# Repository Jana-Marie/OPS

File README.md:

# OPS

OPS is a matchbox sized 65W CC/CV lab power supply. It is controlled by SCPI and powered by USB-PD.

**Please Note that this project is not yet fully tested.**

<table>
  <tbody>
    <tr>
      <td colspan="2">
        
      </td>
    </tr>
    <tr>
      <td>
        
      </td>
      <td>
        
      </td>
    </tr>
    <tr>
      <td colspan="2">
        
      </td>
    </tr>
    <tr>
      <td>
        
      </td>
      <td>
        
      </td>
    </tr>
  </tbody>
</table>

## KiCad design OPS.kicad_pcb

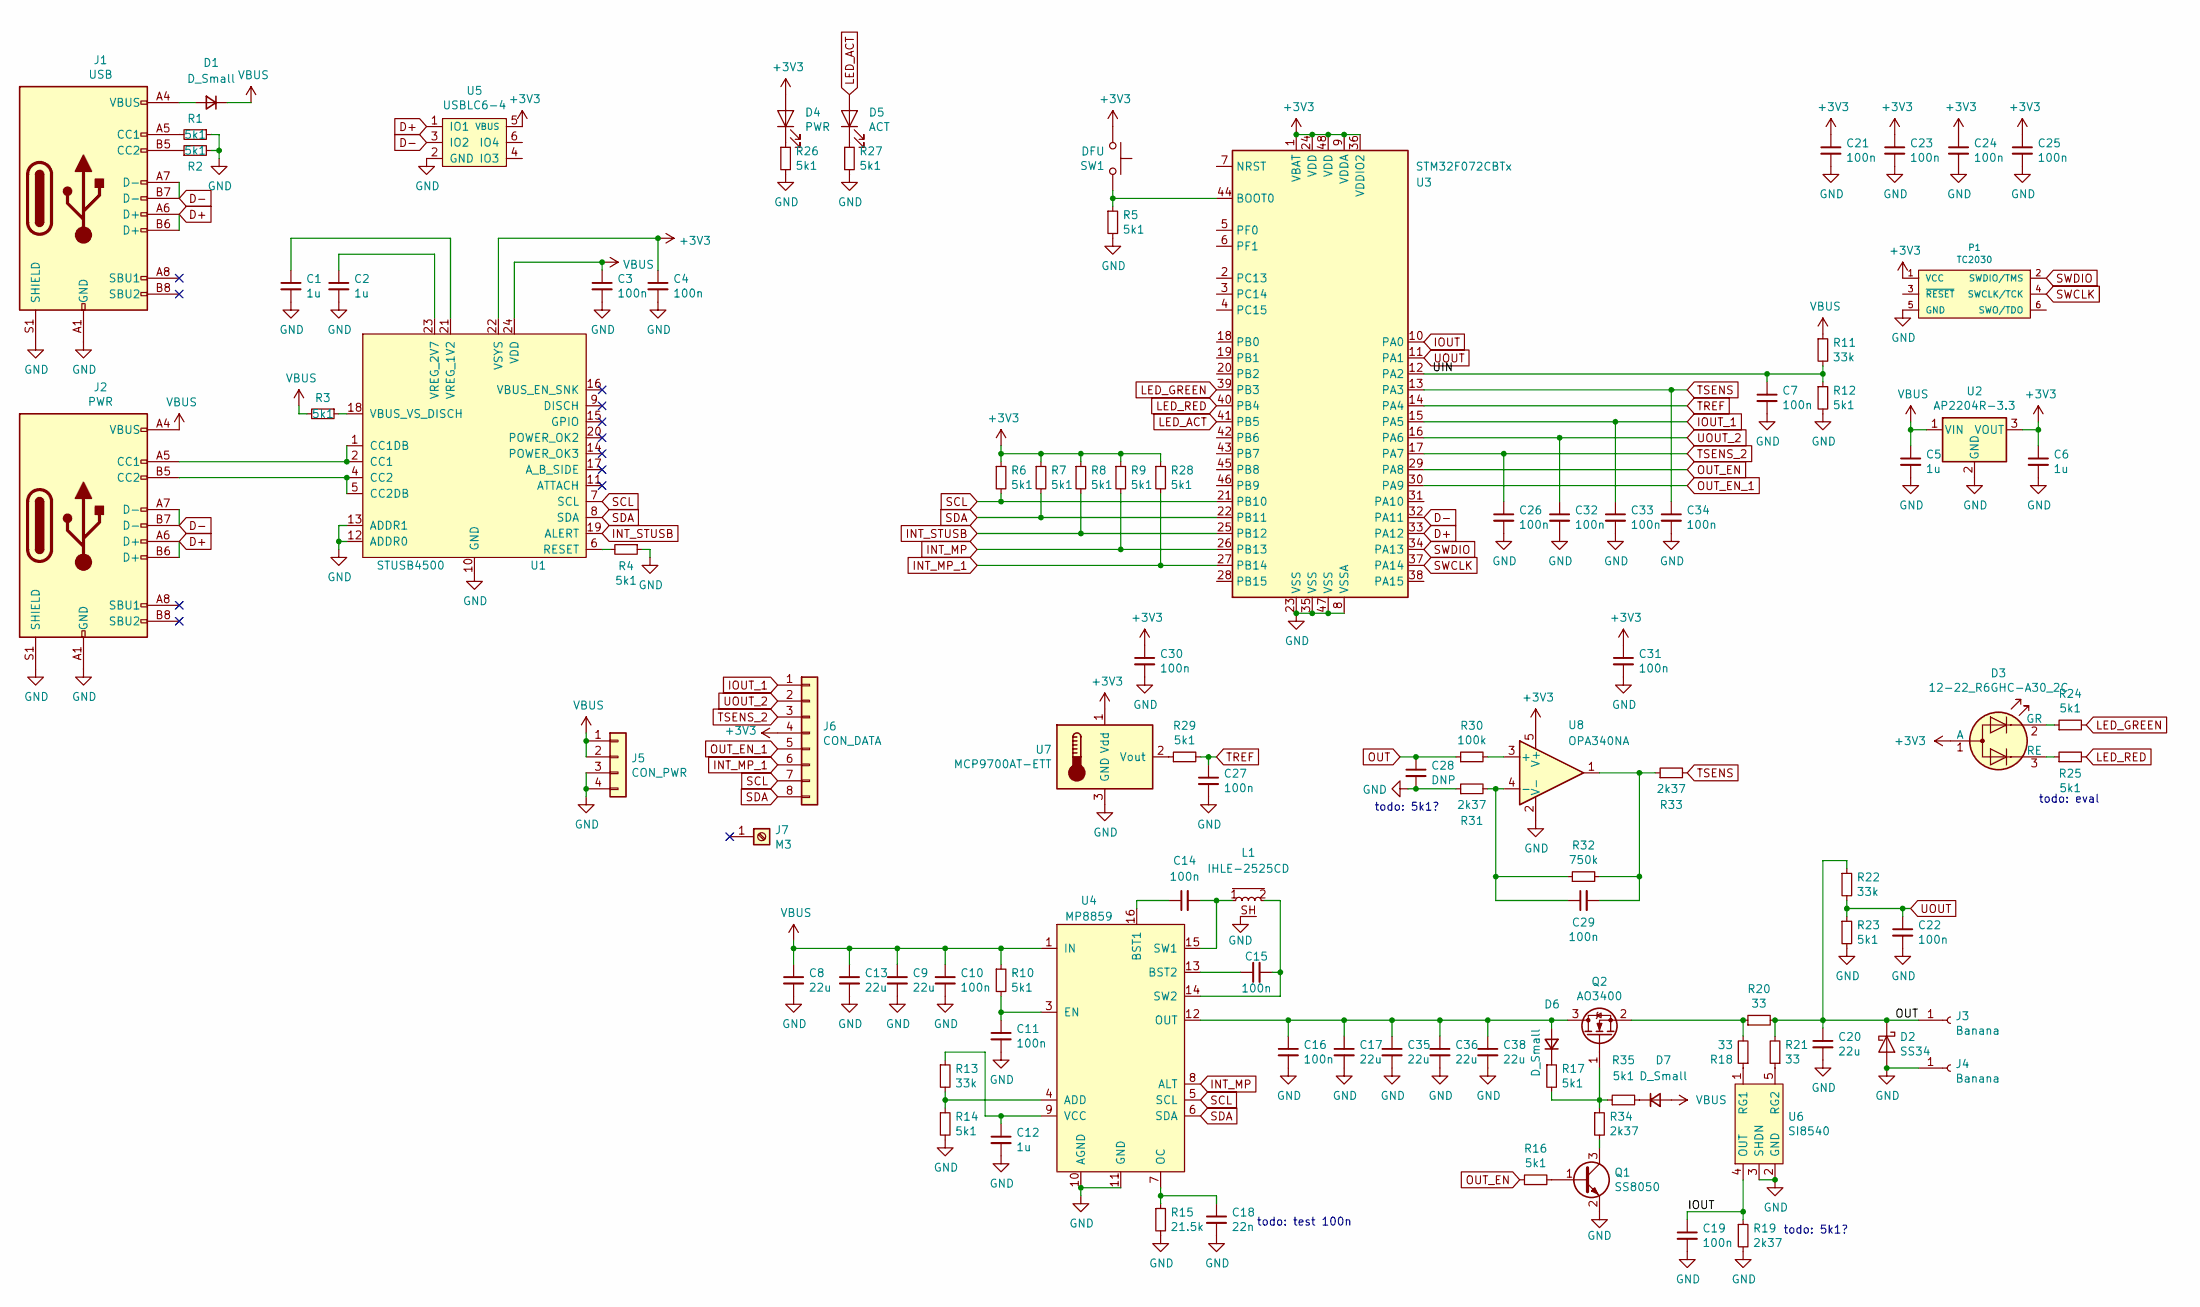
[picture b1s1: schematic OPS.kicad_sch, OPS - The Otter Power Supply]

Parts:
C1, C2, C5, C6, C12: 1u; C_0402
C3, C4, C7, C11, C19, C21, C22, C23, C24, C25, C26, C27, C29, C30, C31, C32, C33, C34: 100n; C_0402
C8, C9, C13, C17, C35, C36, C38: 22u; C_1210
C10, C14, C15, C16: 100n; C_0603
C18: 22n; C_0402
C20: 22u; C_0805
C28: DNP; C_0402
D1, D6, D7: D_Small; D_SOD-323
D2: SS34; D_SOD-123
D3: 12-22_R6GHC-A30_2C; R6GHC-A30
D4: PWR; LED_0603_1608Metric
D5: ACT; LED_0603_1608Metric
J1: USB; USB-C 16Pin
J2: PWR; USB-C 16Pin
J3, J4: Banana; banana-jack
J5: CON_PWR; PinHeader_1x04_P2.00mm_Vertical
J6: CON_DATA; PinHeader_1x08_P2.00mm_Vertical
J7: M3; MountingHole_3.2mm_M3_Pad
L1: IHLE-2525CD
P1: TC2030
Q1: SS8050; SOT-23
Q2: AO3400; SOT-23
R1, R2, R3, R4, R5, R6, R7, R8, R9, R10, R12, R14, R16, R17, R23, R24, R25, R26, R27, R28, R29, R35: 5k1; R_0402
R11, R13, R22: 33k; R_0402
R15: 21.5k; R_0402
R18, R21: 33; R_0402
R19, R31, R33, R34: 2k37; R_0402
R20: 33; R_0805
R30: 100k; R_0402
R32: 750k; R_0402
SW1: DFU; SW_SPST_EVQP7C
U1: STUSB4500; QFN-24-1EP_4x4mm_P0.5mm_EP2.7x2.7mm
U2: AP2204R-3.3; SOT-89-3
U3: STM32F072CBTx; LQFP-48_7x7mm_P0.5mm
U4: MP8859
U5: USBLC6-4; SOT-23-6
U6: SI8540; SOT-23-5
U7: MCP9700AT-ETT; SOT-23
U8: OPA340NA; SOT-23-5

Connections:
+3V3: C4.1, C6.1, C21.1, C23.1, C24.1, C25.1, C30.1, C31.1, D3.1 (A), D4.2 (A), J6.4, P1.1 (VCC), R6.1, R7.1, R8.1, R9.1, R28.1, SW1.1, U1.22 (VSYS), U2.3 (VOUT), U3.1 (VBAT), U3.9 (VDDA), U3.24 (VDD), U3.36 (VDDIO2), U3.48 (VDD), U5.5 (VBUS), U7.1 (Vdd), U8.5 (V+)
/UIN: C7.1, R11.2, R12.1, U3.12 (PA2)
D+: J1.A6 (D+), J1.B6 (D+), J2.A6 (D+), J2.B6 (D+), U3.33 (PA12), U5.1 (IO1)
D-: J1.A7 (D-), J1.B7 (D-), J2.A7 (D-), J2.B7 (D-), U3.32 (PA11), U5.3 (IO2)
GND: C1.2, C2.2, C3.2, C4.2, C5.2, C6.2, C7.2, C8.2, C9.2, C10.2, C11.2, C12.2, C13.2, C16.2, C17.2, C18.2, C19.2, C20.2, C21.2, C22.2, C23.2, C24.2, C25.2, C26.2, C27.2, C28.2, C30.2, C31.2, C32.2, C33.2, C34.2, C35.2, C36.2, C38.2, D2.2 (A), J1.A1 (GND), J1.A12 (GND), J1.B1 (GND), J1.B12 (GND), J1.S1 (SHIELD), J2.A1 (GND), J2.A12 (GND), J2.B1 (GND), J2.B12 (GND), J2.S1 (SHIELD), J4.1, J5.3, J5.4, L1.SH, P1.5 (GND), Q1.2 (E), R1.1, R2.2, R4.1, R5.2, R12.2, R14.2, R15.2, R19.2, R23.2, R26.2, R27.2, R31.1, U1.10 (GND), U1.12 (ADDR0), U1.13 (ADDR1), U1.25 (GND), U2.2 (GND), U3.8 (VSSA), U3.23 (VSS), U3.35 (VSS), U3.47 (VSS), U4.2 (GND), U4.10 (AGND), U4.11 (GND), U5.2 (GND), U6.2 (GND), U6.3 (SHDN), U7.3 (GND), U8.2 (V-)
INT_MP: R9.2, U3.26 (PB13), U4.8 (ALT)
INT_MP_1: J6.6, R28.2, U3.27 (PB14)
INT_STUSB: R8.2, U1.19 (ALERT), U3.25 (PB12)
IOUT: C19.1, R19.1, U3.10 (PA0), U6.4 (OUT)
IOUT_1: C33.1, J6.1, U3.15 (PA5)
LED_ACT: D5.2 (A), U3.41 (PB5)
LED_GREEN: R24.2, U3.39 (PB3)
LED_RED: R25.2, U3.40 (PB4)
unnamed: C1.1, U1.21 (VREG_1V2)
unnamed: C2.1, U1.23 (VREG_2V7)
unnamed: C11.1, R10.2, U4.3 (EN)
unnamed: C12.1, R13.1, U4.9 (VCC)
unnamed: C14.1, U4.16 (BST1)
unnamed: C14.2, L1.1, U4.15 (SW1)
unnamed: C15.1, U4.13 (BST2)
unnamed: C15.2, L1.2, U4.14 (SW2)
unnamed: C16.1, C17.1, C35.1, C36.1, C38.1, D6.2 (A), Q2.3 (D), U4.12 (OUT)
unnamed: C18.1, R15.1, U4.7 (OC)
unnamed: C29.1, R31.2, R32.1, U8.4 (-)
unnamed: C29.2, R32.2, R33.1, U8.1
unnamed: D1.2 (A), J1.A4 (VBUS), J1.A9 (VBUS), J1.B4 (VBUS), J1.B9 (VBUS)
unnamed: D3.2 (GR), R24.1
unnamed: D3.3 (RE), R25.1
unnamed: D4.1 (K), R26.1
unnamed: D5.1 (K), R27.1
unnamed: D6.1 (K), R17.1
unnamed: D7.1 (K), R35.2
unnamed: J1.A5 (CC1), R1.2
unnamed: J1.B5 (CC2), R2.1
unnamed: J2.A5 (CC1), U1.1 (CC1DB), U1.2 (CC1)
unnamed: J2.B5 (CC2), U1.4 (CC2), U1.5 (CC2DB)
unnamed: Q1.1 (B), R16.2
unnamed: Q1.3 (C), R34.2
unnamed: Q2.1 (G), R17.2, R34.1, R35.1
unnamed: Q2.2 (S), R18.2, R20.1
unnamed: R3.1, U1.18 (VBUS_VS_DISCH)
unnamed: R4.2, U1.6 (RESET)
unnamed: R5.1, SW1.2, U3.44 (BOOT0)
unnamed: R13.2, R14.1, U4.4 (ADD)
unnamed: R18.1, U6.1 (RG1)
unnamed: R21.1, U6.5 (RG2)
unnamed: R29.1, U7.2 (Vout)
unnamed: R30.2, U8.3 (+)
OUT: C20.1, C28.1, D2.1 (K), J3.1, R20.2, R21.2, R22.1, R30.1
OUT_EN: R16.1, U3.29 (PA8)
OUT_EN_1: J6.5, U3.30 (PA9)
SCL: J6.7, R6.2, U1.7 (SCL), U3.21 (PB10), U4.5 (SCL)
SDA: J6.8, R7.2, U1.8 (SDA), U3.22 (PB11), U4.6 (SDA)
SWCLK: P1.4 (SWCLK/TCK), U3.37 (PA14)
SWDIO: P1.2 (SWDIO/TMS), U3.34 (PA13)
TREF: C27.1, R29.2, U3.14 (PA4)
TSENS: C34.1, R33.2, U3.13 (PA3)
TSENS_2: C26.1, J6.3, U3.17 (PA7)
UOUT: C22.1, R22.2, R23.1, U3.11 (PA1)
UOUT_2: C32.1, J6.2, U3.16 (PA6)
VBUS: C3.1, C5.1, C8.1, C9.1, C10.1, C13.1, D1.1 (K), D7.2 (A), J2.A4 (VBUS), J2.A9 (VBUS), J2.B4 (VBUS), J2.B9 (VBUS), J5.1, J5.2, R3.2, R10.1, R11.1, U1.24 (VDD), U2.1 (VIN), U4.1 (IN)

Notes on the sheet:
todo: 5k1?
todo: eval
todo: test 100n

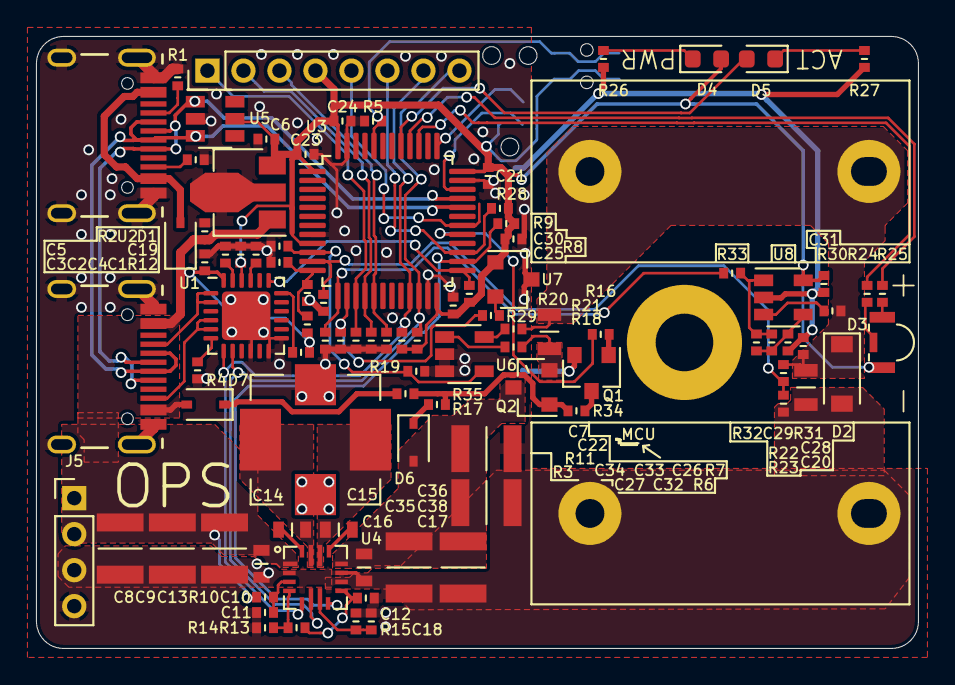
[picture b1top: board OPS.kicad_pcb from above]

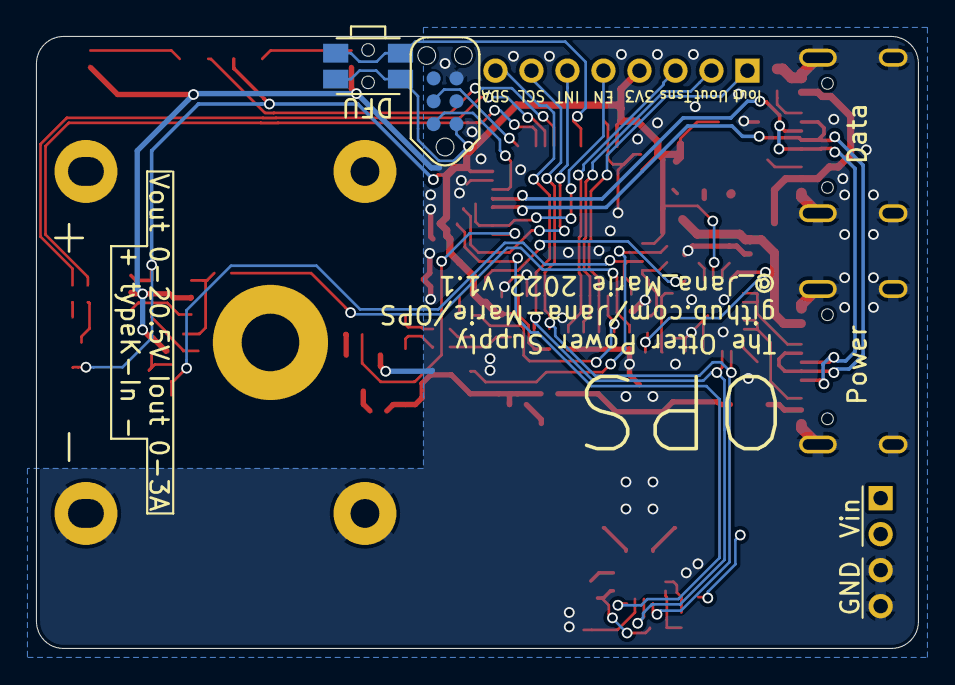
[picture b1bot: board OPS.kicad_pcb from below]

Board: 2 copper layers, 49.0 x 34.0 mm, 99 parts (2 on the bottom side), 61 nets.

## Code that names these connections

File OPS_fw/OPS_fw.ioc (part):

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Mcu.Name=STM32F072C(8-B)Tx
Mcu.Package=LQFP48
Mcu.UserName=STM32F072CBTx
PA0.Mode=IN0
PA0.Signal=ADC_IN0
PA1.Mode=IN1
PA1.Signal=ADC_IN1
PA11.Mode=Device
PA11.Signal=USB_DM
PA12.Mode=Device
PA12.Signal=USB_DP
PA13.Mode=Serial_Wire
PA13.Signal=SYS_SWDIO
PA14.Mode=Serial_Wire
PA14.Signal=SYS_SWCLK
PA2.Mode=IN2
PA2.Signal=ADC_IN2
PA3.Mode=IN3
PA3.Signal=ADC_IN3
PA4.Mode=IN4
PA4.Signal=ADC_IN4
PA5.Mode=IN5
PA5.Signal=ADC_IN5
PA6.Mode=IN6
PA6.Signal=ADC_IN6
PA7.Mode=IN7
PA7.Signal=ADC_IN7
PA8.GPIOParameters=GPIO_Label
PA8.GPIO_Label=OUT_EN_1
PA8.Signal=GPIO_Output
PA9.GPIOParameters=GPIO_Label
PA9.GPIO_Label=OUT_EN_2
PA9.Signal=GPIO_Output
PB10.Mode=I2C
PB10.Signal=I2C2_SCL
PB11.Mode=I2C
PB11.Signal=I2C2_SDA
PB12.GPIOParameters=GPIO_Label
PB12.GPIO_Label=INT_STUSB
PB12.Signal=GPXTI12
PB13.GPIOParameters=GPIO_Label
PB13.GPIO_Label=INT_MP_1
PB13.Signal=GPXTI13
PB14.GPIOParameters=GPIO_Label
PB14.GPIO_Label=INT_MP_2
PB14.Signal=GPXTI14
PB3.GPIOParameters=GPIO_Label
PB3.GPIO_Label=LED_GREEN
PB3.Signal=GPIO_Output
PB4.GPIOParameters=GPIO_Label
PB4.GPIO_Label=LED_RED
PB4.Signal=GPIO_Output
PB5.GPIOParameters=GPIO_Label
PB5.GPIO_Label=LED_ACT
PB5.Signal=GPIO_Output
RCC.SYSCLKFreq_VALUE=48000000
RCC.SYSCLKSource=RCC_SYSCLKSOURCE_HSI48
board=custom

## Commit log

2021-04-19 started layout
2021-04-26 routing 60%
2021-04-26 routing 99%
2021-04-26 silk
2021-12-30 updated silk
2022-01-05 updated to kicad 6
2022-01-05 initial fw commit, everything works, except the output mosfet, it needs to be removed from the design
2022-01-11 removed binaries
2022-09-01 updated layout, exchanged PMIC caps and inductor
2022-09-01 updated gerber
2022-09-01 added gitignore
2022-09-01 removed backups
2022-09-01 updated gitignore
2022-09-01 removed cache
2022-09-01 removed bom
2022-09-01 updated fw
2023-04-21 remved gerber
2023-04-21 fixed colspan
2023-04-21 added more images
